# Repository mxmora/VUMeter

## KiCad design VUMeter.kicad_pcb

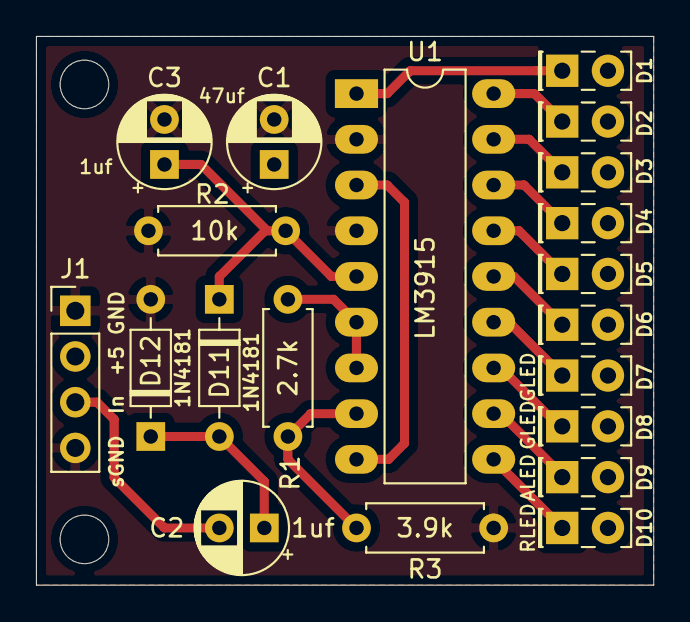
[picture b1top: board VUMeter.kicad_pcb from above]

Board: 2 copper layers, 34.3 x 30.5 mm, 22 parts (0 on the bottom side), 17 nets.

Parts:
C1: 47uf; CP_Radial_D5.0mm_P2.50mm
C2, C3: 1uf; CP_Radial_D5.0mm_P2.50mm
D1, D2, D3, D4, D5, D6, D7: GLED; LED_Rectangular_W5.0mm_H2.0mm
D8, D9: ALED; LED_Rectangular_W5.0mm_H2.0mm
D10: RLED; LED_Rectangular_W5.0mm_H2.0mm
D11, D12: 1N4181; D_DO-35_SOD27_P7.62mm_Horizontal
H1, H2: MountingHole; MountingHole_2.7mm_M2.5_DIN965
J1: Conn_01x04_Male; PinHeader_1x04_P2.54mm_Vertical
R1: 2.7k; R_Axial_DIN0207_L6.3mm_D2.5mm_P7.62mm_Horizontal
R2: 10k; R_Axial_DIN0207_L6.3mm_D2.5mm_P7.62mm_Horizontal
R3: 3.9k; R_Axial_DIN0207_L6.3mm_D2.5mm_P7.62mm_Horizontal
U1: LM3915; DIP-18_W7.62mm_LongPads

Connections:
+5V: C1.1, D1.2, D2.2, D3.2, D4.2, D5.2, D6.2, D7.2, D8.2, D9.2, D10.2, J1.2, U1.3, U1.9
GND: C1.2, C3.2, D12.2, J1.1, J1.4, R2.2, R3.2, U1.2, U1.4
unnamed: C2.1, D11.2, D12.1
unnamed: C2.2, J1.3
unnamed: C3.1, D11.1, R2.1, U1.5
unnamed: D1.1, U1.1
unnamed: D2.1, U1.18
unnamed: D3.1, U1.17
unnamed: D4.1, U1.16
unnamed: D5.1, U1.15
unnamed: D6.1, U1.14
unnamed: D7.1, U1.13
unnamed: D8.1, U1.12
unnamed: D9.1, U1.11
unnamed: D10.1, U1.10
unnamed: R1.1, U1.6, U1.7
unnamed: R1.2, R3.1, U1.8

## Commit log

2019-08-30 first add of files
2019-09-07 update parts
2019-09-07 update for new PCB layout
